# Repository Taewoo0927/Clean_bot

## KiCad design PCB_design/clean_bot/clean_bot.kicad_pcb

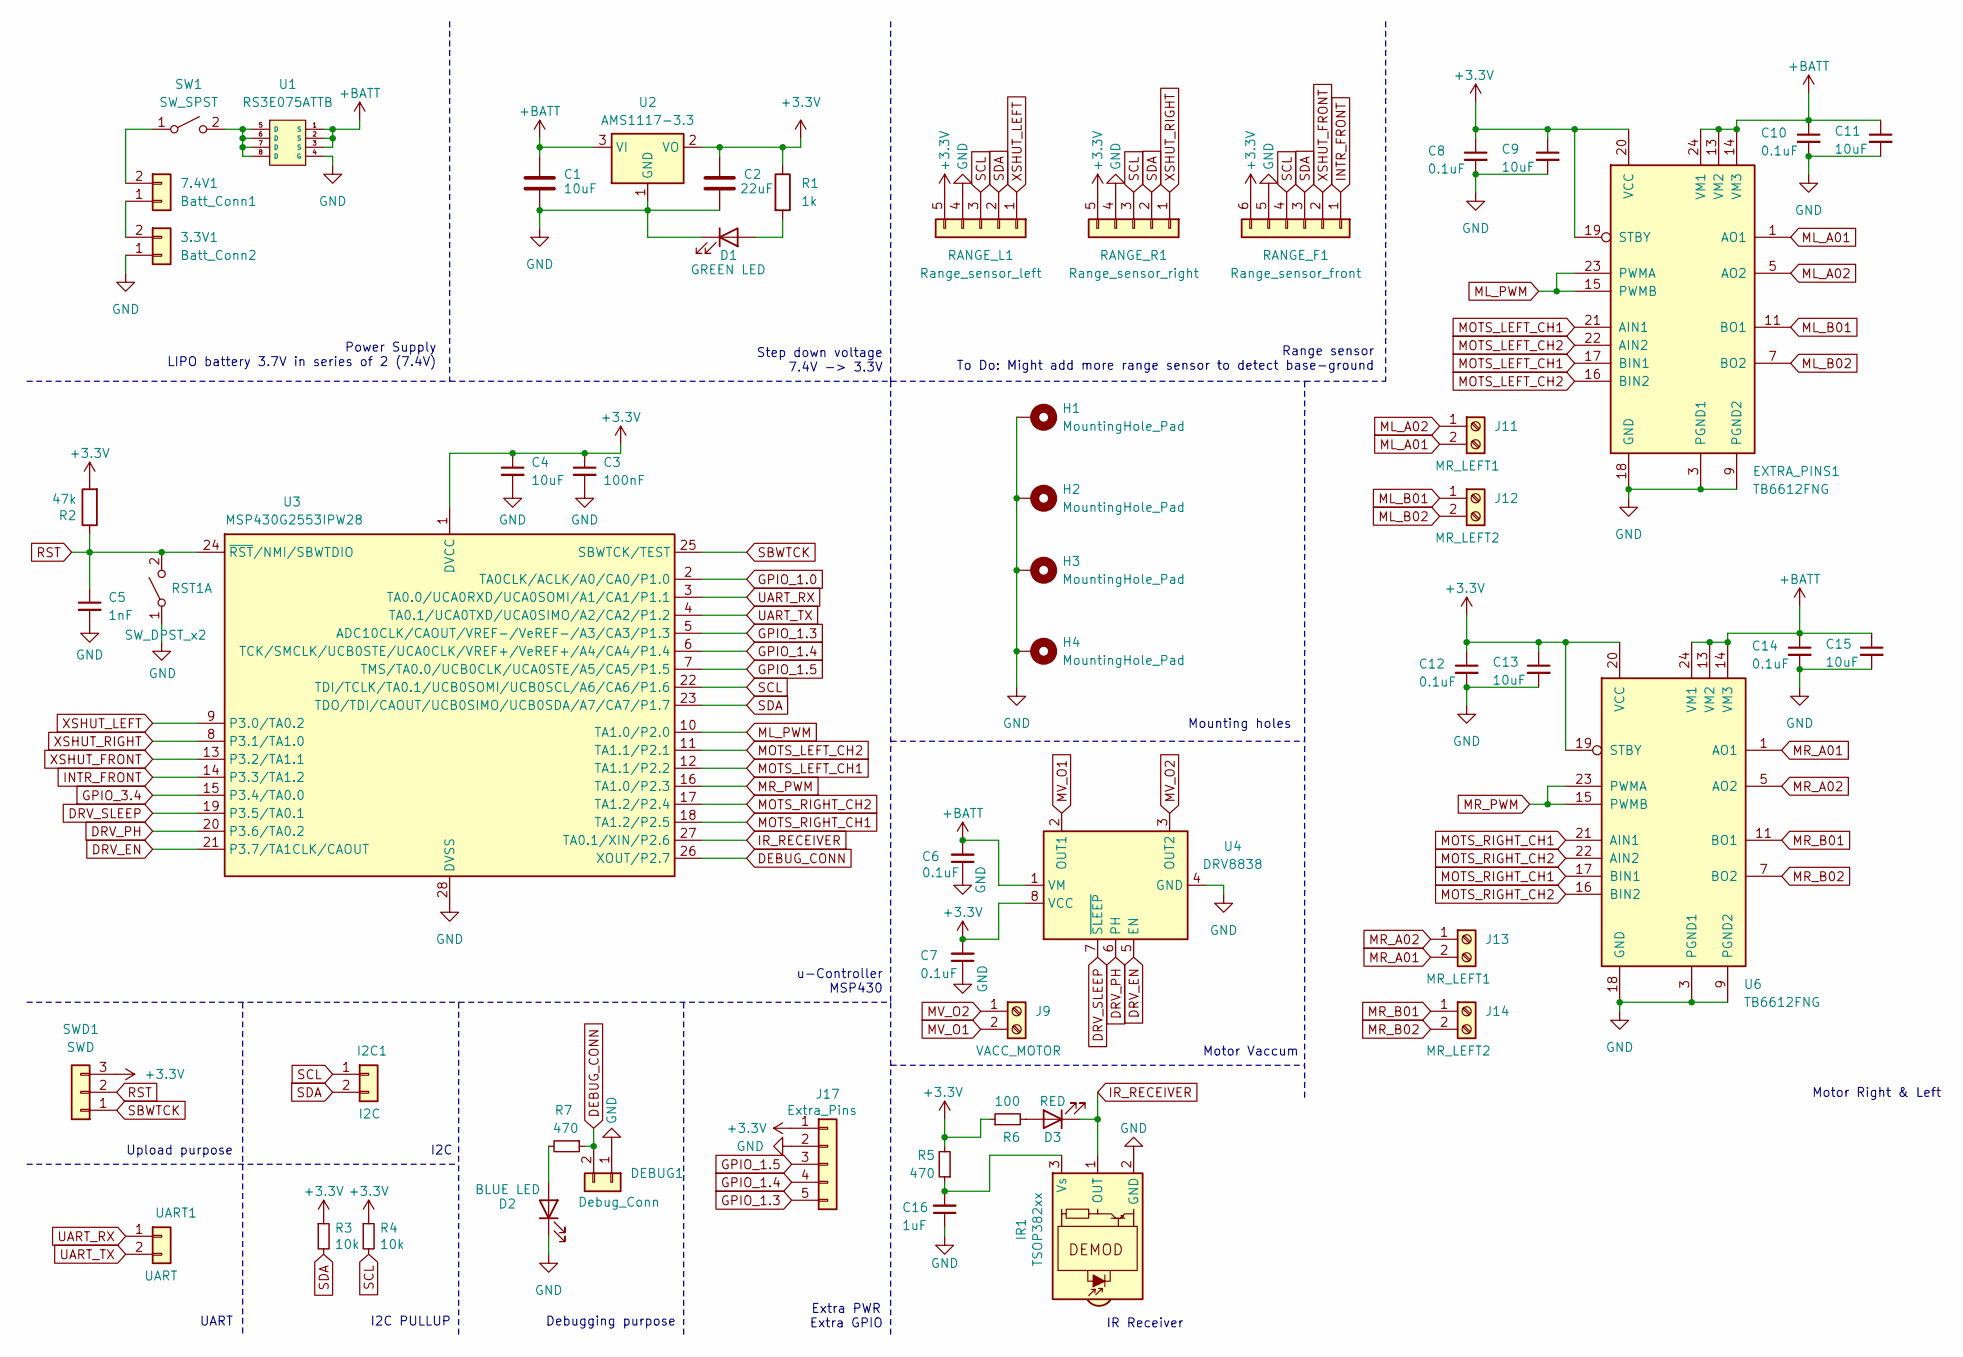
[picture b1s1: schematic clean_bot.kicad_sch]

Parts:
3.3V1: Batt_Conn2; Hirose_DF13-02P-1.25DS_1x02_P1.25mm_Horizontal
7.4V1: Batt_Conn1; Hirose_DF13-02P-1.25DS_1x02_P1.25mm_Horizontal
C1: 10uF; C_0805_2012Metric
C2: 22uF; C_0805_2012Metric
C3: 100nF; C_0603_1608Metric
C4: 10uF; C_0201_0603Metric
C5: 1nF; C_0201_0603Metric
C6, C7: 0.1uF; C_0201_0603Metric
C8, C10, C12, C14: 0.1uF; C_0805_2012Metric; LCSC Part C49678
C9, C11, C13, C15: 10uF; C_0805_2012Metric; LCSC Part C15850
C16: 1uF; C_0201_0603Metric
D1: GREEN LED; LED_0603_1608Metric
D2: BLUE LED; LED_0603_1608Metric
D3: RED; LED_0603_1608Metric; LCSC Part C2286
DEBUG1: Debug_Conn; PinHeader_1x02_P2.54mm_Vertical
EXTRA_PINS1: TB6612FNG; SSOP-24_5.3x8.2mm_P0.65mm
H1, H2, H3, H4: MountingHole_Pad; MountingHole_2.2mm_M2_Pad_Via
I2C1: I2C; PinHeader_1x02_P2.54mm_Vertical
IR1: TSOP382xx; Vishay_MINICAST-3Pin
J9: VACC_MOTOR; CUI_TB002-500-02BE
J11, J13: MR_LEFT1; CUI_TB002-500-02BE
J12, J14: MR_LEFT2; CUI_TB002-500-02BE
J17: Extra_Pins; PinHeader_1x05_P2.54mm_Vertical
R1: 1k; R_0805_2012Metric
R2: 47k; R_0603_1608Metric; LCSC Part C25819
R3, R4: 10k; R_1206_3216Metric; LCSC Part C17902
R5, R7: 470; R_0805_2012Metric; LCSC Part C17710
R6: 100; R_0805_2012Metric; LCSC Part C17408
RANGE_F1: Range_sensor_front; Molex_PicoBlade_53048-0610_1x06_P1.25mm_Horizontal
RANGE_L1: Range_sensor_left; Molex_PicoBlade_53048-0510_1x05_P1.25mm_Horizontal
RANGE_R1: Range_sensor_right; Molex_PicoBlade_53048-0510_1x05_P1.25mm_Horizontal
RST1: SW_DPST_x2; SW_Push_1P1T_NO_6x6mm_H9.5mm
SW1: SW_SPST; PinHeader_1x02_P2.54mm_Vertical
SWD1: SWD; PinHeader_1x03_P2.54mm_Vertical
U1: RS3E075ATTB; TRANS_RRH040P_ROM
U2: AMS1117-3.3; SOT-223-3_TabPin2
U3: MSP430G2553IPW28; TSSOP-28_4.4x9.7mm_P0.65mm
U4: DRV8838; WSON-8-1EP_2x2mm_P0.5mm_EP0.9x1.6mm
U6: TB6612FNG; SSOP-24_5.3x8.2mm_P0.65mm
UART1: UART; PinHeader_1x02_P2.54mm_Vertical

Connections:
+3.3V: C2.1, C3.1, C4.1, C7.2, C8.1, C9.1, C12.1, C13.1, EXTRA_PINS1.19 (STBY), EXTRA_PINS1.20 (VCC), J17.1, R1.1, R2.2, R3.1, R4.1, R5.2, R6.1, RANGE_F1.6, RANGE_L1.5, RANGE_R1.5, SWD1.3, U2.2 (VO), U3.1 (DVCC), U4.8 (VCC), U6.19 (STBY), U6.20 (VCC)
+BATT: C1.1, C6.2, C10.1, C11.1, C14.1, C15.1, EXTRA_PINS1.13 (VM2), EXTRA_PINS1.14 (VM3), EXTRA_PINS1.24 (VM1), U1.1 (S), U1.2 (S), U1.3 (S), U2.3 (VI), U4.1 (VM), U6.13 (VM2), U6.14 (VM3), U6.24 (VM1)
DEBUG_CONN: DEBUG1.2, R7.1, U3.26 (XOUT/P2.7)
DRV_EN: U3.21 (P3.7/TA1CLK/CAOUT), U4.5 (EN)
DRV_PH: U3.20 (P3.6/TA0.2), U4.6 (PH)
DRV_SLEEP: U3.19 (P3.5/TA0.1), U4.7 (~SLEEP)
GND: 3.3V1.1, C1.2, C2.2, C3.2, C4.2, C5.2, C6.1, C7.1, C8.2, C9.2, C10.2, C11.2, C12.2, C13.2, C14.2, C15.2, C16.1, D1.1 (K), D2.1 (K), DEBUG1.1, EXTRA_PINS1.3 (PGND1), EXTRA_PINS1.4 (PGND1), EXTRA_PINS1.9 (PGND2), EXTRA_PINS1.10 (PGND2), EXTRA_PINS1.18 (GND), H1.1, H2.1, H3.1, H4.1, IR1.2 (GND), J17.2, RANGE_F1.5, RANGE_L1.4, RANGE_R1.4, RST1.1 (A), U1.4 (G), U2.1 (GND), U3.28 (DVSS), U4.4 (GND), U4.9 (GND), U6.3 (PGND1), U6.4 (PGND1), U6.9 (PGND2), U6.10 (PGND2), U6.18 (GND)
GPIO_1.0: U3.2 (TA0CLK/ACLK/A0/CA0/P1.0)
GPIO_1.3: J17.5, U3.5 (ADC10CLK/CAOUT/VREF-/VeREF-/A3/CA3/P1.3)
GPIO_1.4: J17.4, U3.6 (TCK/SMCLK/UCB0STE/UCA0CLK/VREF+/VeREF+/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)
GPIO_1.5: J17.3, U3.7 (TMS/TA0.0/UCB0CLK/UCA0STE/A5/CA5/P1.5)
GPIO_3.4: U3.15 (P3.4/TA0.0)
INTR_FRONT: RANGE_F1.1, U3.14 (P3.3/TA1.2)
IR_RECEIVER: D3.1 (K), IR1.1 (OUT), U3.27 (TA0.1/XIN/P2.6)
ML_A01: EXTRA_PINS1.1 (AO1), EXTRA_PINS1.2 (AO1), J11.2
ML_A02: EXTRA_PINS1.5 (AO2), EXTRA_PINS1.6 (AO2), J11.1
ML_B01: EXTRA_PINS1.11 (BO1), EXTRA_PINS1.12 (BO1), J12.1
ML_B02: EXTRA_PINS1.7 (BO2), EXTRA_PINS1.8 (BO2), J12.2
ML_PWM: EXTRA_PINS1.15 (PWMB), EXTRA_PINS1.23 (PWMA), U3.10 (TA1.0/P2.0)
MOTS_LEFT_CH1: EXTRA_PINS1.17 (BIN1), EXTRA_PINS1.21 (AIN1), U3.12 (TA1.1/P2.2)
MOTS_LEFT_CH2: EXTRA_PINS1.16 (BIN2), EXTRA_PINS1.22 (AIN2), U3.11 (TA1.1/P2.1)
MOTS_RIGHT_CH1: U3.18 (TA1.2/P2.5), U6.17 (BIN1), U6.21 (AIN1)
MOTS_RIGHT_CH2: U3.17 (TA1.2/P2.4), U6.16 (BIN2), U6.22 (AIN2)
MR_A01: J13.2, U6.1 (AO1), U6.2 (AO1)
MR_A02: J13.1, U6.5 (AO2), U6.6 (AO2)
MR_B01: J14.1, U6.11 (BO1), U6.12 (BO1)
MR_B02: J14.2, U6.7 (BO2), U6.8 (BO2)
MR_PWM: U3.16 (TA1.0/P2.3), U6.15 (PWMB), U6.23 (PWMA)
MV_O1: J9.2, U4.2 (OUT1)
MV_O2: J9.1, U4.3 (OUT2)
unnamed: 3.3V1.2, 7.4V1.1
unnamed: 7.4V1.2, SW1.1 (A)
unnamed: D1.2 (A), R1.2
unnamed: D2.2 (A), R7.2
unnamed: D3.2 (A), R6.2
unnamed: C16.2, IR1.3 (Vs), R5.1
unnamed: SW1.2 (B), U1.5 (D), U1.6 (D), U1.7 (D), U1.8 (D)
RST: C5.1, R2.1, RST1.2 (B), SWD1.2, U3.24 (~RST/NMI/SBWTDIO)
SBWTCK: SWD1.1, U3.25 (SBWTCK/TEST)
SCL: I2C1.1, R4.2, RANGE_F1.4, RANGE_L1.3, RANGE_R1.3, U3.22 (TDI/TCLK/TA0.1/UCB0SOMI/UCB0SCL/A6/CA6/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)
SDA: I2C1.2, R3.2, RANGE_F1.3, RANGE_L1.2, RANGE_R1.2, U3.23 (TDO/TDI/CAOUT/UCB0SIMO/UCB0SDA/A7/CA7/P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)
UART_RX: U3.3 (TA0.0/UCA0RXD/UCA0SOMI/A1/CA1/P1.1), UART1.1
UART_TX: U3.4 (TA0.1/UCA0TXD/UCA0SIMO/A2/CA2/P1.2), UART1.2
XSHUT_FRONT: RANGE_F1.2, U3.13 (P3.2/TA1.1)
XSHUT_LEFT: RANGE_L1.1, U3.9 (P3.0/TA0.2)
XSHUT_RIGHT: RANGE_R1.1, U3.8 (P3.1/TA1.0)

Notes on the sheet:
I2C
Motor Vaccum
Power Supply LIPO battery 3.7V in series of 2 (7.4V)
Extra PWR
UART
I2C PULLUP
Range sensor To Do: Might add more range sensor to detect base-ground
u-Controller MSP430
Upload purpose
Motor Right & Left
Debugging purpose
Extra GPIO
Step down voltage 7.4V -> 3.3V
IR Receiver
Mounting holes

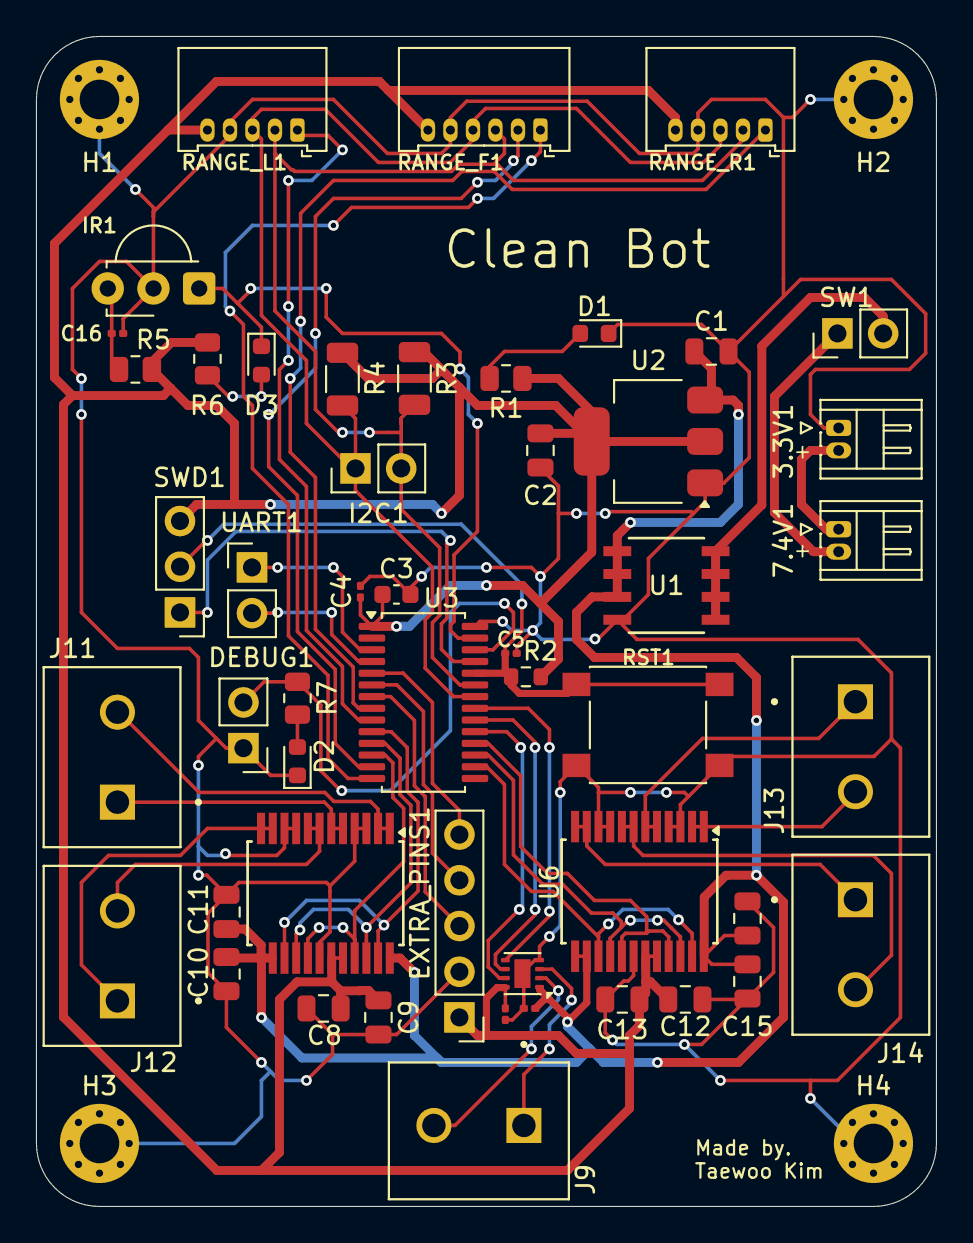
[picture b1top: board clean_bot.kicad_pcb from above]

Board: 2 copper layers, 50.0 x 65.0 mm, 54 parts (0 on the bottom side), 44 nets.

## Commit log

2024-11-16 Add files via upload
    <First commit>
    Started on state machine diagram.
    Contains three main state: Search, Retreat, Move
2024-11-16 <RetreatState> Additional state diagram for Retreat Statement
2024-11-16 <Folders> Chnaged folder structures
2024-11-16 <Folders> Updated folder names and uml names
2024-11-16 <PCB> Commiting pcb designs for clean bot
2024-11-17 <Instruction steps> 1. Add steps how that I connected msp430 to vsc 2. Initial Json file without using make file
2024-11-17 <Foundation files> 1. main.c : testing with blinking LED 2. json files : tasks to use run commands, updaed include linker script paths. 3. Makefile : to intergrate commands that will be called from t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
2024-11-17 <Updated Makefile> 1. updated it to make build folder to locate main.elf and main.txt
2024-11-17 <Folders> 1. Updated location of the files
2024-11-17 <Updated folders> 1. Added project setup documentation file
2024-11-17 <Makefile, PlantUML> 1. Added the reset vector so code start right away 2. Added the UML diagram to write down steps of process of hardware in simple steps
2024-11-17 <Makefile> 1. simple codes to create Makefile
2024-11-17 <io.h, io.c> 1. Added io.h, io.c 2. need to modify Makefile & cproperties so compiler can find io.h
2024-11-17 <Testing io.h> 1. It's not including io.h properly
2024-11-17 <Makefile> 1. Added json command so it can build-flash in one go makefile
2024-11-17 <Makefile, io.h> 1. Added additional Git.mk for consistent CI pipeline. 2. Tested io.h with typedef enum.
2024-11-17 [A[A[B[B
2024-11-17 Auto-commit from Makefile
2024-11-17 <Makefile> 1. Testing purpose for including git.mk to makefile main. 2. added additional feature git-pull
2024-11-17 <Makefile> 1. Updated git.mk to do pull-commit-push process in one go
2024-11-18 <Makefile, documentation> 1. Upadated small bugs inside Git.mk such as user.name and user.email 2. Add pipeline plantuml to make it easier to show project pipeline
2024-11-18 <Makefile> 1. Testing individual commit
2024-11-18 <Makefile> 1. Another testing
2024-11-18 <Makefile> 1. Testing another git-commit
2024-11-18 <Makefile> 1.git-init - to initialize in the beginning setupt
2024-11-18 <<Makefile> 1. This is testing for demo
2024-11-19 <Makefile> 1. Added cppcheck static analyzer for CI pipeline
2024-11-21 <Makefile> 1. Updated my makefile to make it work in gitaction. Gitaction uses ubuntu which is linux setting but my pc is windows so I checked OS and changed paths to environmental variable if it's g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
2024-11-21 Create ci.yml
    <Ci.yml>
    1. Need to figure out how I can set tool chains for msp430
2024-11-22 Update ci.yml
    <Added docker>
    1. Docker is added since I need toolchain for msp430 to build the code for to run cppcheck
2024-11-22 <Dockerfile> 1. Pushing dockerfile that I created to build the toolchains for msp430g2553 and test the CI pipeline that is created using gitaction
2024-11-22 <Ci.yml> 1. Changed the syntaxing error in -uses took out "-"
2024-11-22 <ci.yml> 1. Defined the makefile directory properly
2024-11-22 <ci.yml> 1. Changed the folder direction for cppcheck as well
2024-11-22 <Main.c> 1. Removed unnecessary function to test my CI pipeline
2024-11-22 <Makefile> 1. Fixed makefile to run cppcheck properly for example if cppcheck doesn't find any warnings that match the suppression, it generates an unmatchedSuppression message.
2024-11-22 <Test branch> 1. Testing pull request to check if my pipeline is working properly
2024-11-22 <Main> 1. checking CI for main branch
2024-11-22 <Test branch>
    1. changed makefile for linux setting as msp430 since it's using msp430 (docker) instead of msp430-gcc
2024-11-22 <Makefile> 1. Thrid trial to test ci and Makefile. Added: selective toolchains for docker(gitaction), main build
2024-11-22 <Debug> 1. Add debugging step to list ldscripts directory
2024-11-22 <Debug> 1. Added extra debug feature
2024-11-22 <Debug> 1. Added comments for Makefile debug features and splited the location settings for linux(gitaction) and windows.
2024-11-23 <To do> 1. Added to do to makefile
2024-11-24 <io.h, to-do> 1. added io_sel and io_dir register blocks in the header file. 2. added to-do list to track what I need to do
2024-11-27 <io.h> 1. added new function definitions and typedef enum for ren, out, in registers
2024-11-28 <io.h> 1. commiting test
2024-11-30 <pdf> 1. Added manual and datasheet for the msp430g2553 for the reference.
2024-11-30 test commit
2024-11-30 <io.c> 1. Created mask for port
2024-12-24 <io.h, io.c> 1. Created io_set_sel function to choose which mode I want to use pin as. Also used Lookup table to optimize the function
    2. Organized reference folder
2024-12-24 <io.c> 1. Finished function of io_sel, io_dir, io_op, io_res, and io_ip
2024-12-24 <io.c, main.c> 1. optimized io.c 2. created blink_led
2024-12-24 testing
2024-12-24 CHECKING IF IT WORKS PROPERLY
2024-12-24 <main.c>
2024-12-24 <main.c> 1. Debugging to check if io.c is working or not
2024-12-24 <main.c> debugging
2024-12-24 <main.c> debugg
2024-12-24 <main.c> debug
2024-12-24 <main.c> debug lookup table and io.c on the main.c
2024-12-24 <io.c> 1. Fixed #define IO_PORT(io) by subtraction 1, it is due to Lookuptable array indexing. 0 corresponds to P1 and 1 corresponds to P2 so after extracting port number it need to be subtracted by 1
2024-12-24 <To_Do> 1. Added what to do next time
2024-12-25 <main.c, io.c> 1. added structure for configuring the pins 2. tested on main.c by static function
2024-12-25 <main.c> 1. added sturct to configure pins easier
2024-12-25 <main.c> 1. Used intrinsic delay cycle function instead of for loop
2024-12-25 <main.c> 1. testing how much time it takes per cycle
2024-12-25 <main.c> 1. checking exact 1ms to create accurate cycle
2024-12-25 <main.c> 1. optimizing delay function
2024-12-25 <main.c> 1. making cycles accurate for the delay function
2024-12-25 <Other.c,.h> 1. created separate other.c to store useful functions that will might reused in the future
2024-12-25 <others.c> 1. making accurate
2024-12-25 <others.c> changed to 16bit[1;5D[1;5D[1;5D[1;5D[1;5D[1;5D[1;5D[1;5D[1;5D[1;5D[1;5D[1;5D[1;5D[1;5D[1;5D[1;5D1. changed input to 16bit
2024-12-25 <system_init.c> 1. encapsulated watchdog to make main function more readable
2024-12-28 <Updated>
2024-12-28 <io.c>
2024-12-28 <io.c>
    1. Created function name io_init to configure all the io in default
2024-12-28 <Comments> 1. Added extra comments to explain io_init and array_size in others.c
2024-12-28 <main.c> 1. formatted better
2024-12-28 test
2024-12-28 test2
2024-12-28 <Img> 1. added software architecutre image
2024-12-28 <main.c> 1. added the way to test all the pins in output mode using logic analyzer
2024-12-28 <main.c> 1. added the way to test all the io in output mode
2024-12-28 <test.c> 1. separated test functions from main.c
2024-12-28 <test.c>: Final commit 1. separated test.c from main.c by creating new folder named Test 2. By using logic analyzer (ad2), checked all the io pins work as output mode
2024-12-28 <C99> 1. testing c99 error
2024-12-28 <pin_test_branch> 1. added -std=c99 to avoid weird error such as " 'for' loop initial declarations are only allowed in C99 mode"
2024-12-28 <pin_test_branch> : Final commit 1. Fixed all the issue and added test function
2024-12-28 <pin_test_branch>: Final commit 1. Fixed all the issue and added test function
2024-12-28 <Testing memory allocation>
2024-12-29 <Makefile> 1. Added size_detail command to check function memory allocation
2024-12-29 <Makefile, test.c> 1. reduced the function
2024-12-29 <Interrupt> 1. creating interrupt configuration functions
2025-01-05 <io.c> 1. Basic set up for the Interrupt
2025-01-10 <io.c, test.c> 1. Created interrupt vector table 2. Created interrupt configuration 3. Created interrupt test function
2025-01-10 <test.c> 1. debugging the interrupt since it's not triggering properly
2025-01-10 <io.c, test.c> 1. Debugging interrupt functions
2025-01-10 <Test.C, io.C> 1. Figured out that I have issue on the lookup table instead of P1IE i wrote P2IE
2025-01-10 <Test.c>
    1. working now
